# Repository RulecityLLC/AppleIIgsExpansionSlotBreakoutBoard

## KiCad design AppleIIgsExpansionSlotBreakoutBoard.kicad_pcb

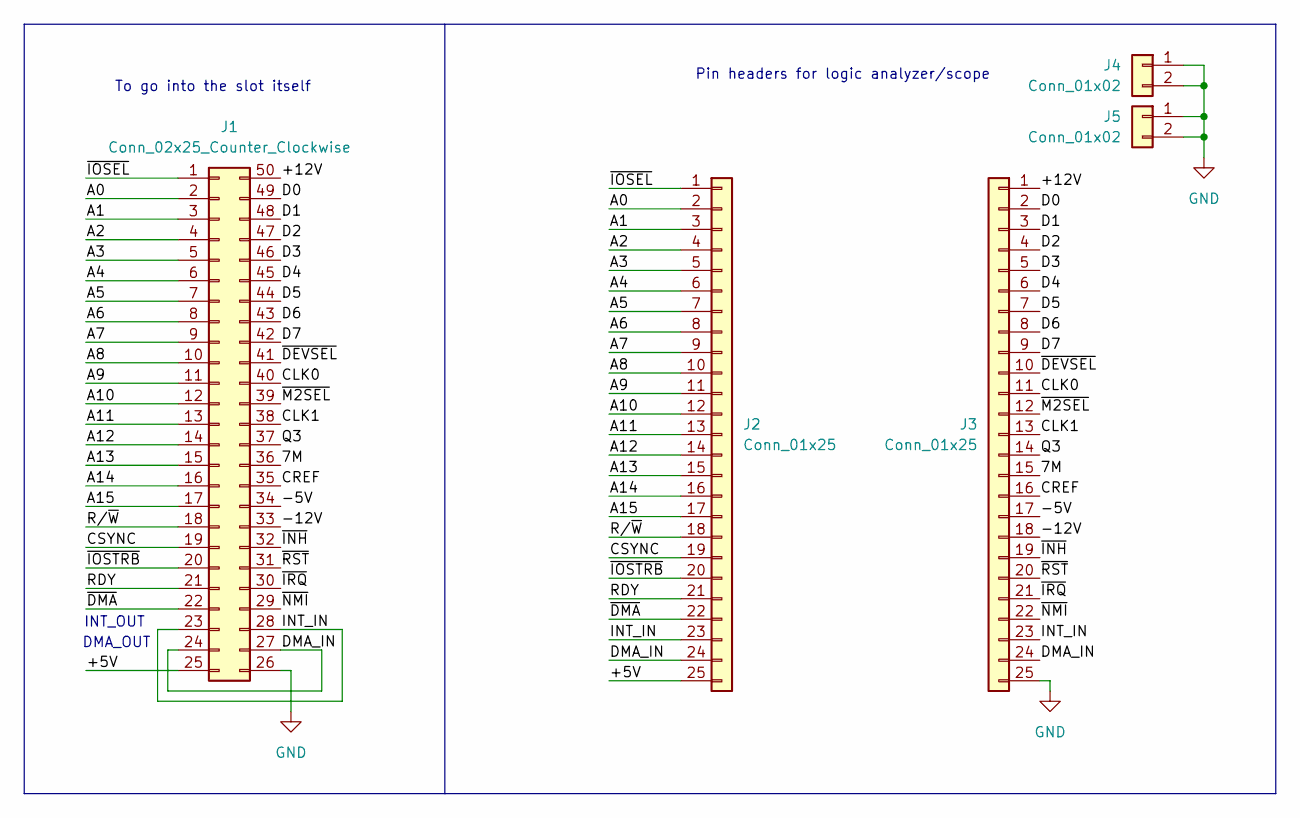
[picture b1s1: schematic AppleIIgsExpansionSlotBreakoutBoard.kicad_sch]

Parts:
J1: Conn_02x25_Counter_Clockwise; Apple II Expansion Edge Connector
J2, J3: Conn_01x25; PinHeader_1x25_P2.54mm_Vertical
J4, J5: Conn_01x02; PinHeader_1x02_P2.54mm_Vertical

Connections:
/7M: J1.36, J3.15
/+5V: J1.25, J2.25
/+12V: J1.50, J3.1
/-5V: J1.34, J3.17
/-12V: J1.33, J3.18
/A0: J1.2, J2.2
/A1: J1.3, J2.3
/A2: J1.4, J2.4
/A3: J1.5, J2.5
/A4: J1.6, J2.6
/A5: J1.7, J2.7
/A6: J1.8, J2.8
/A7: J1.9, J2.9
/A8: J1.10, J2.10
/A9: J1.11, J2.11
/A10: J1.12, J2.12
/A11: J1.13, J2.13
/A12: J1.14, J2.14
/A13: J1.15, J2.15
/A14: J1.16, J2.16
/A15: J1.17, J2.17
/CLK0: J1.40, J3.11
/CLK1: J1.38, J3.13
/CREF: J1.35, J3.16
/CSYNC: J1.19, J2.19
/D0: J1.49, J3.2
/D1: J1.48, J3.3
/D2: J1.47, J3.4
/D3: J1.46, J3.5
/D4: J1.45, J3.6
/D5: J1.44, J3.7
/D6: J1.43, J3.8
/D7: J1.42, J3.9
/DMA_IN: J1.24, J1.27, J2.24, J3.24
/INT_IN: J1.23, J1.28, J2.23, J3.23
/Q3: J1.37, J3.14
/RDY: J1.21, J2.21
/R/~W: J1.18, J2.18
/~DEVSEL: J1.41, J3.10
/~DMA: J1.22, J2.22
/~INH: J1.32, J3.19
/~IOSEL: J1.1, J2.1
/~IOSTRB: J1.20, J2.20
/~IRQ: J1.30, J3.21
/~M2SEL: J1.39, J3.12
/~NMI: J1.29, J3.22
/~RST: J1.31, J3.20
GND: J1.26, J3.25, J4.1, J4.2, J5.1, J5.2

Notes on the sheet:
Pin headers for logic analyzer/scope
To go into the slot itself
DMA_OUT
INT_OUT

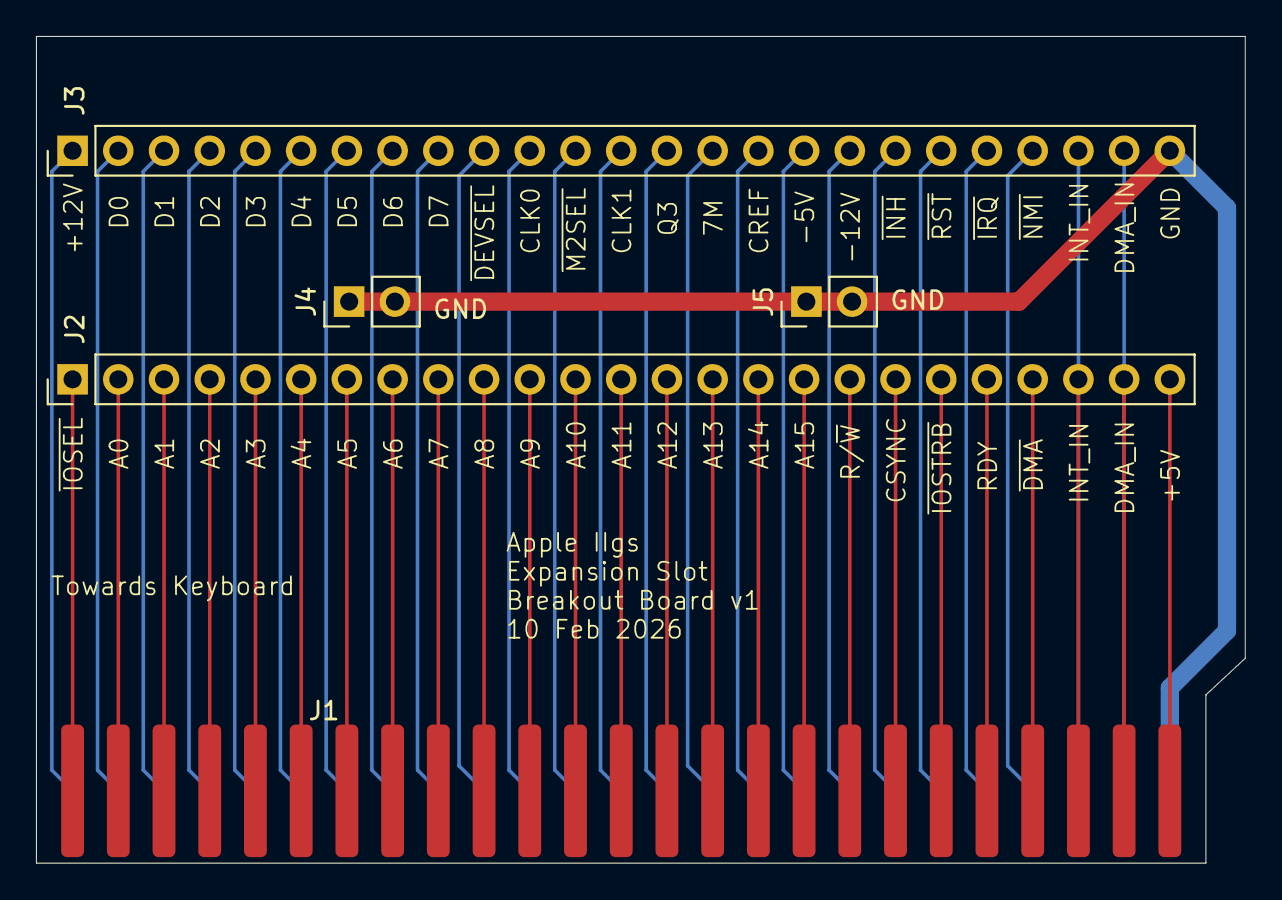
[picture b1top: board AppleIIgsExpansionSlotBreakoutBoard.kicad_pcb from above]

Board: 2 copper layers, 67.2 x 45.9 mm, 5 parts (0 on the bottom side), 48 nets.

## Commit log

2026-02-11 fixed DNA and INT lines not being connected. cleaned up violations.
